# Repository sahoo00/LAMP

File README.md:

# LAMP
A RT-LAMP device for quantitative mRNA measurement at home

## General Info
This folder has EAGLE files for a hardware device that can measure mRNA
at home. There are two modules: Camera and LAMP. Arduino codes, 
Board and Schematic files
for both these modules are provided. CAM processor outputs of all the files
are provided in CAMOutputs.

## Software requirements
Project is created with
* EAGLE
* Adobe Illustrator
* Fusion 360
* Arduino IDE

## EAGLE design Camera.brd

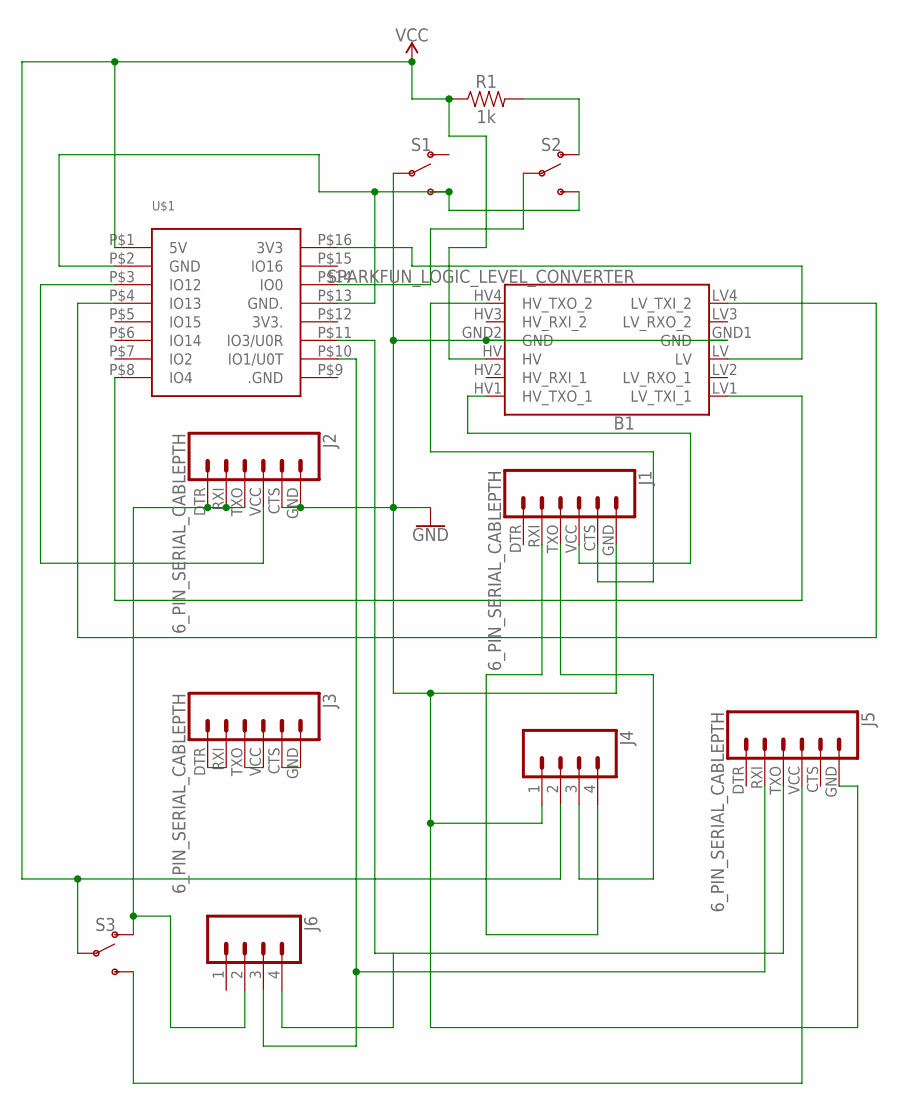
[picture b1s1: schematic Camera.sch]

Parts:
B1: SPARKFUN_LOGIC_LEVEL_CONVERTER
J1, J2, J3, J5: 6_PIN_SERIAL_CABLEPTH; FTDI_BASIC
J4, J6: CONN_04PTH; 1X04
R1: 1k; AXIAL-0.3-KIT
S1, S2, S3: SWITCH-SPDT-PTH-11.6X4.0MM; SWITCH_SPDT_PTH_11.6X4.0MM
U$1: ESP32-CAM

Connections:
GND: B1.GND1 (GND), B1.GND2 (GND), J1.GND (6), J2.CTS (5), J2.GND (6), J4.1, J5.GND (6), S1.2
unnamed: R1.P$2 (2), S2.1 (O)
unnamed: S1.3 (S), S2.3 (S), U$1.P$2 (GND), U$1.P$13 (GND.)
unnamed: J3.DTR (1), J3.RXI (2)
unnamed: S2.2, U$1.P$14 (IO0)
unnamed: J3.TXO (3), J3.VCC (4)
unnamed: B1.LV1 (LV_TXI_1), U$1.P$8 (IO4)
unnamed: B1.LV4 (LV_TXI_2), U$1.P$4 (IO13)
unnamed: J3.CTS (5), J3.GND (6)
unnamed: J2.VCC (4), U$1.P$3 (IO12)
unnamed: B1.HV1 (HV_TXO_1), J1.VCC (4)
unnamed: B1.HV4 (HV_TXO_2), J1.CTS (5)
unnamed: J1.RXI (2), J4.4
unnamed: J1.TXO (3), J4.3
unnamed: B1.LV, U$1.P$16 (3V3)
unnamed: J5.TXO (3), J6.4, U$1.P$11 (IO3/U0R)
unnamed: J5.RXI (2), J6.3, U$1.P$10 (IO1/U0T)
unnamed: J2.DTR (1), J2.RXI (2), J2.TXO (3), J6.2, S3.1 (O)
unnamed: J5.VCC (4), S3.3 (S)
VCC: B1.HV, J4.2, R1.P$1 (1), S3.2, U$1.P$1 (5V)

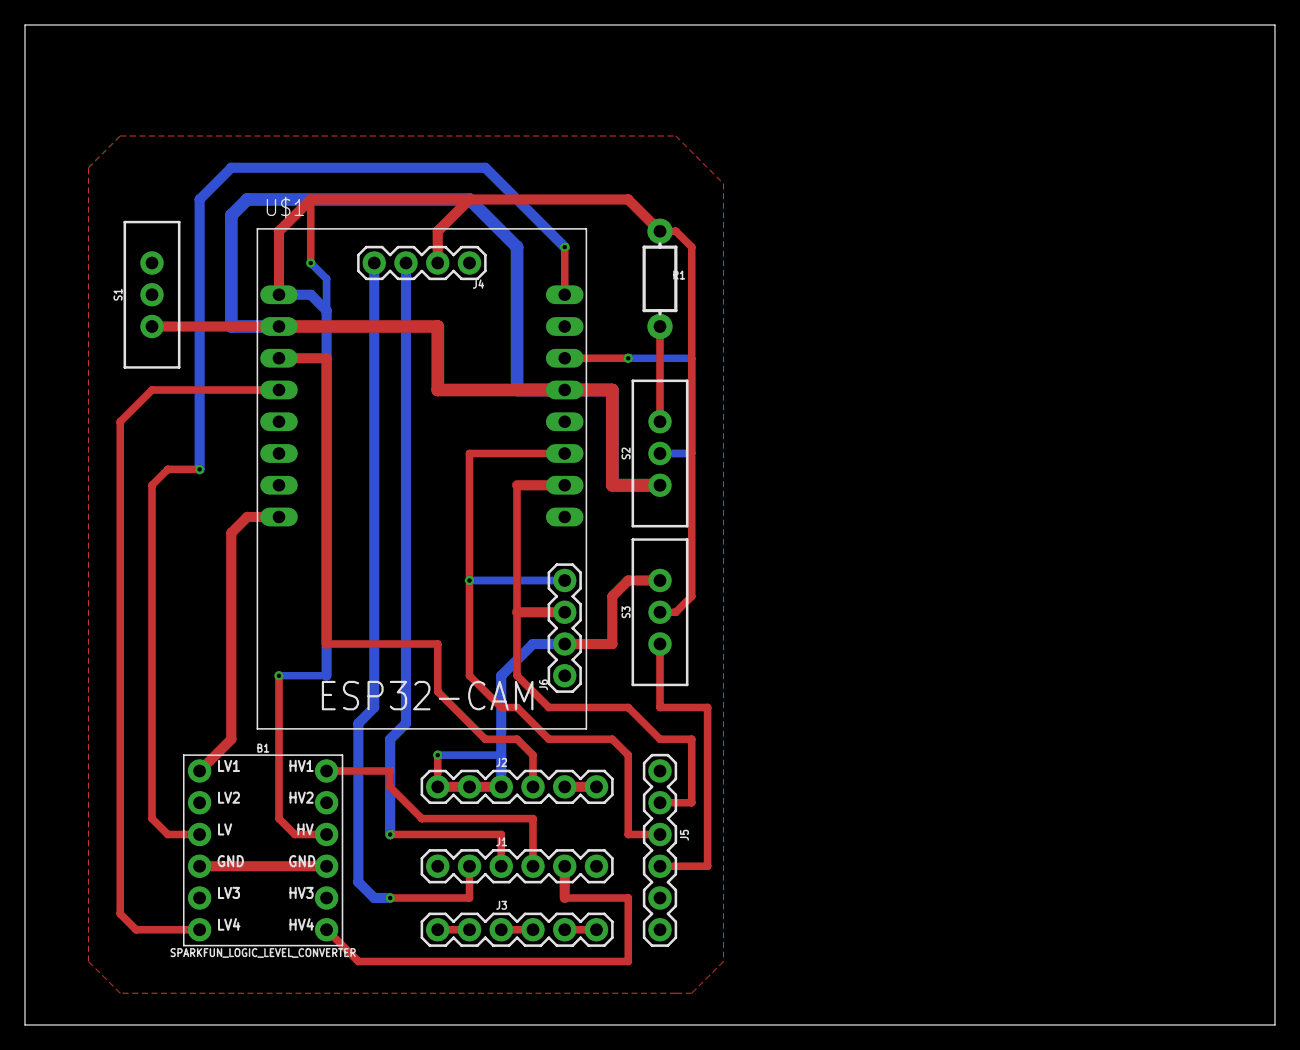
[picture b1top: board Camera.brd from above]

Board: 2 copper layers, 100.0 x 80.0 mm, 12 parts (0 on the bottom side), 20 nets.

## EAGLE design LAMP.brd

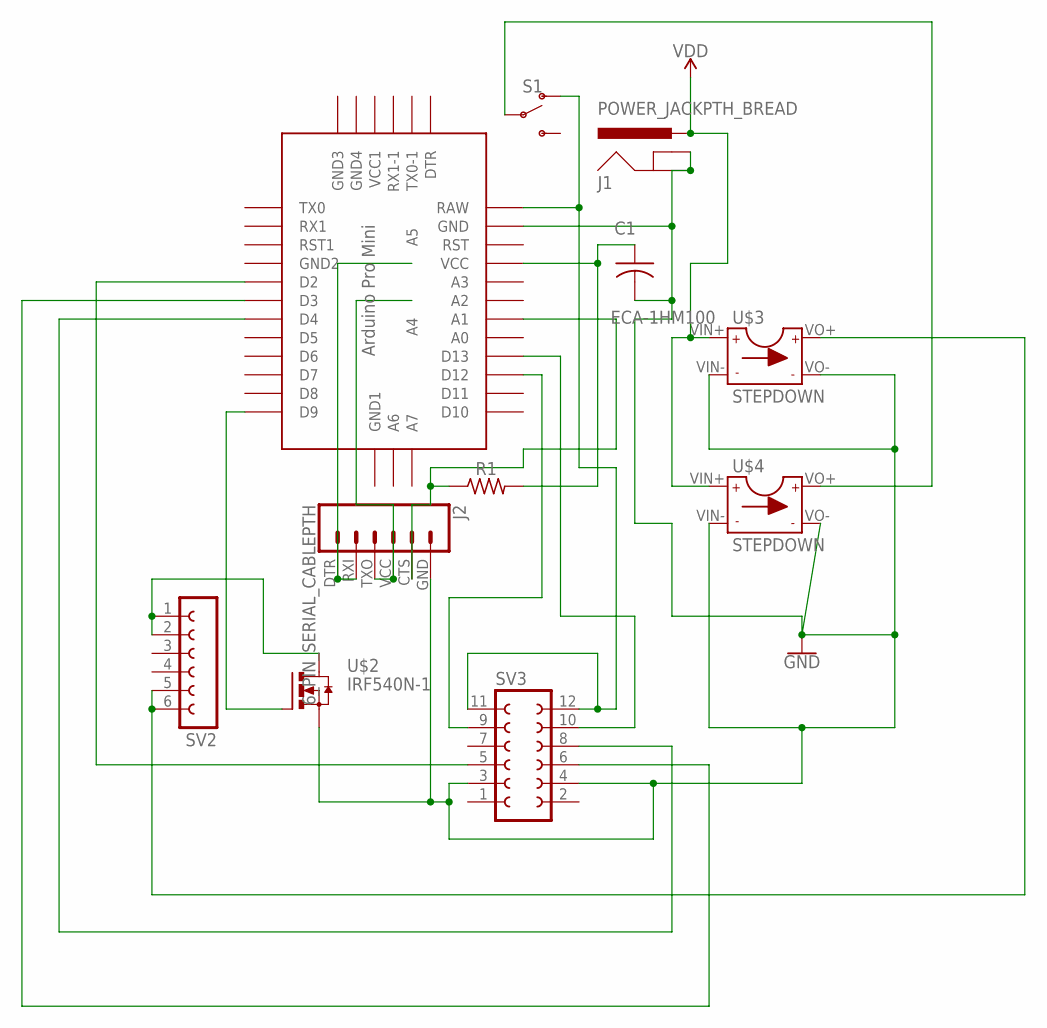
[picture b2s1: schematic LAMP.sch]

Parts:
C1: ECA-1HM100; CAP_RADIAL_2MM
J1: POWER_JACKPTH_BREAD; POWER_JACK_PTH_BREAD
J2: 6_PIN_SERIAL_CABLEPTH; FTDI_BASIC
R1: 1k; V234/12
S1: SWITCH-SPDT-PTH-11.6X4.0MM; SWITCH_SPDT_PTH_11.6X4.0MM
SV2: FE06-1; FE06
SV3: FE06-2
U$1: ABK-PRO-MINI-2
U$2: IRF540N-1; 1X03
U$3, U$4: STEPDOWN; STEPDOWN-1

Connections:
GND: C1.2, J1.GND, J1.GNDBREAK, J2.GND (6), SV3.3, SV3.4, U$1.GND, U$2.3 (S), U$3.VIN-, U$3.VO-, U$4.VIN-, U$4.VO-
unnamed: S1.2, U$4.VO+
unnamed: S1.1 (O), SV3.11, SV3.12, U$1.RAW
unnamed: SV2.1, SV2.2, U$2.2 (D)
unnamed: J2.DTR (1), J2.RXI (2), U$1.A5
unnamed: U$1.D9, U$2.1 (G)
unnamed: SV3.9, U$1.D12
unnamed: SV2.5, SV2.6, U$3.VO+
unnamed: SV3.10, U$1.D13
unnamed: J2.CTS (5), R1.1, U$1.A1
unnamed: C1.1, R1.2, U$1.VCC
unnamed: SV3.5, U$1.D2
unnamed: SV3.6, U$1.D3
unnamed: SV3.8, U$1.D4
unnamed: J2.TXO (3), J2.VCC (4), U$1.A4
VDD: J1.PWR, U$3.VIN+, U$4.VIN+

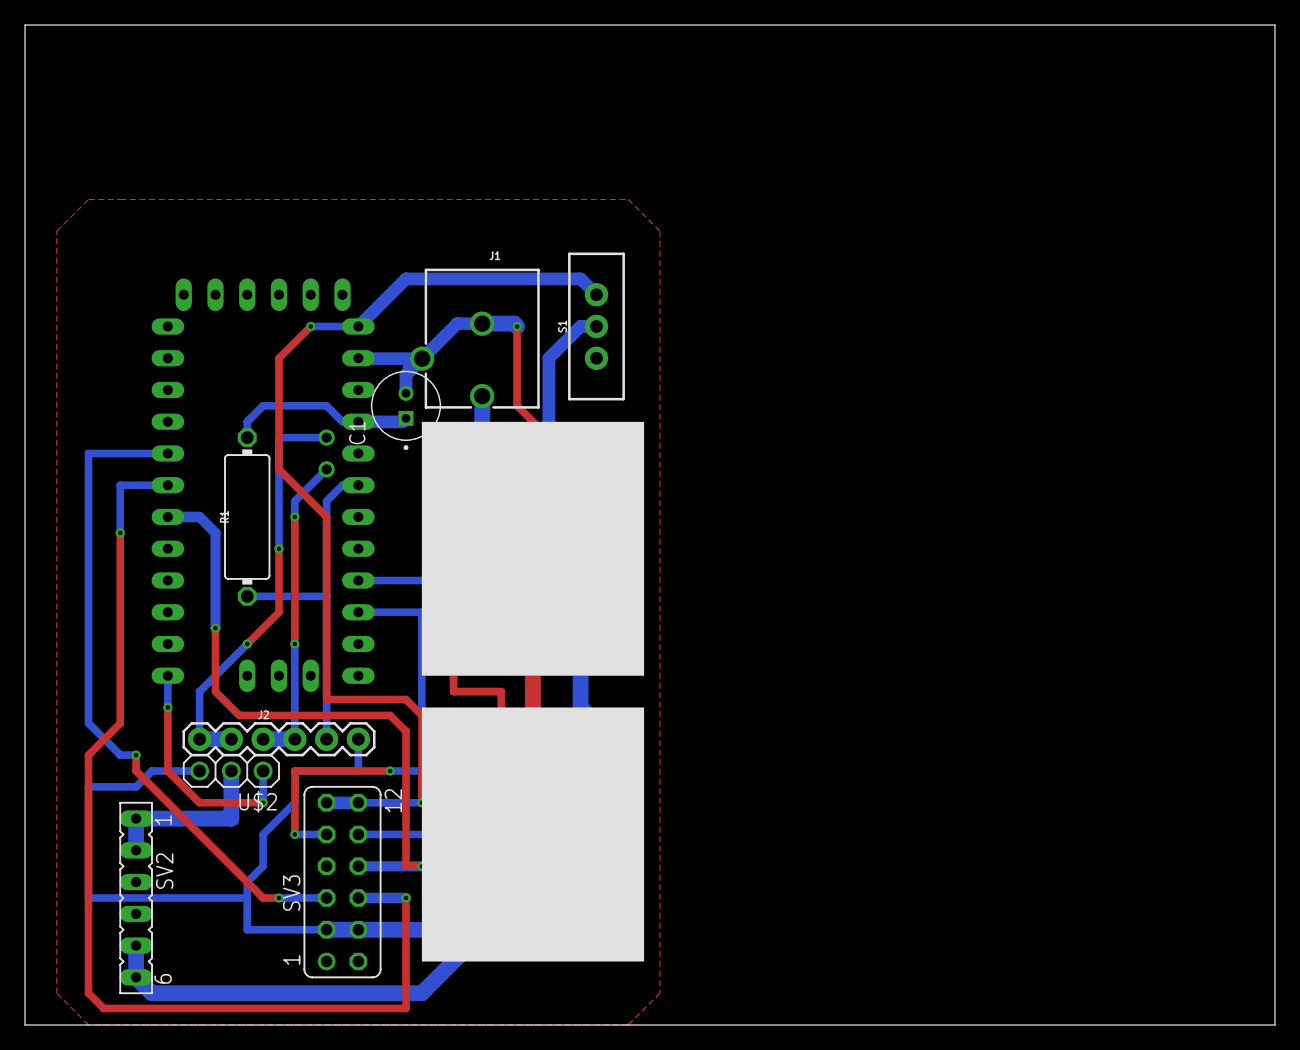
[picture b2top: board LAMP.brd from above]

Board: 2 copper layers, 100.0 x 80.0 mm, 11 parts (0 on the bottom side), 16 nets.

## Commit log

2023-07-09 LAMP Device
2023-07-09 Arduino Codes
2023-07-09 Shanvi renamed

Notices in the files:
parts and their libraries:
SparkFun-Switches: Licensing: Creative Commons ShareAlike 4.0 International - https://creativecommons.org/licenses/by-sa/4.0
